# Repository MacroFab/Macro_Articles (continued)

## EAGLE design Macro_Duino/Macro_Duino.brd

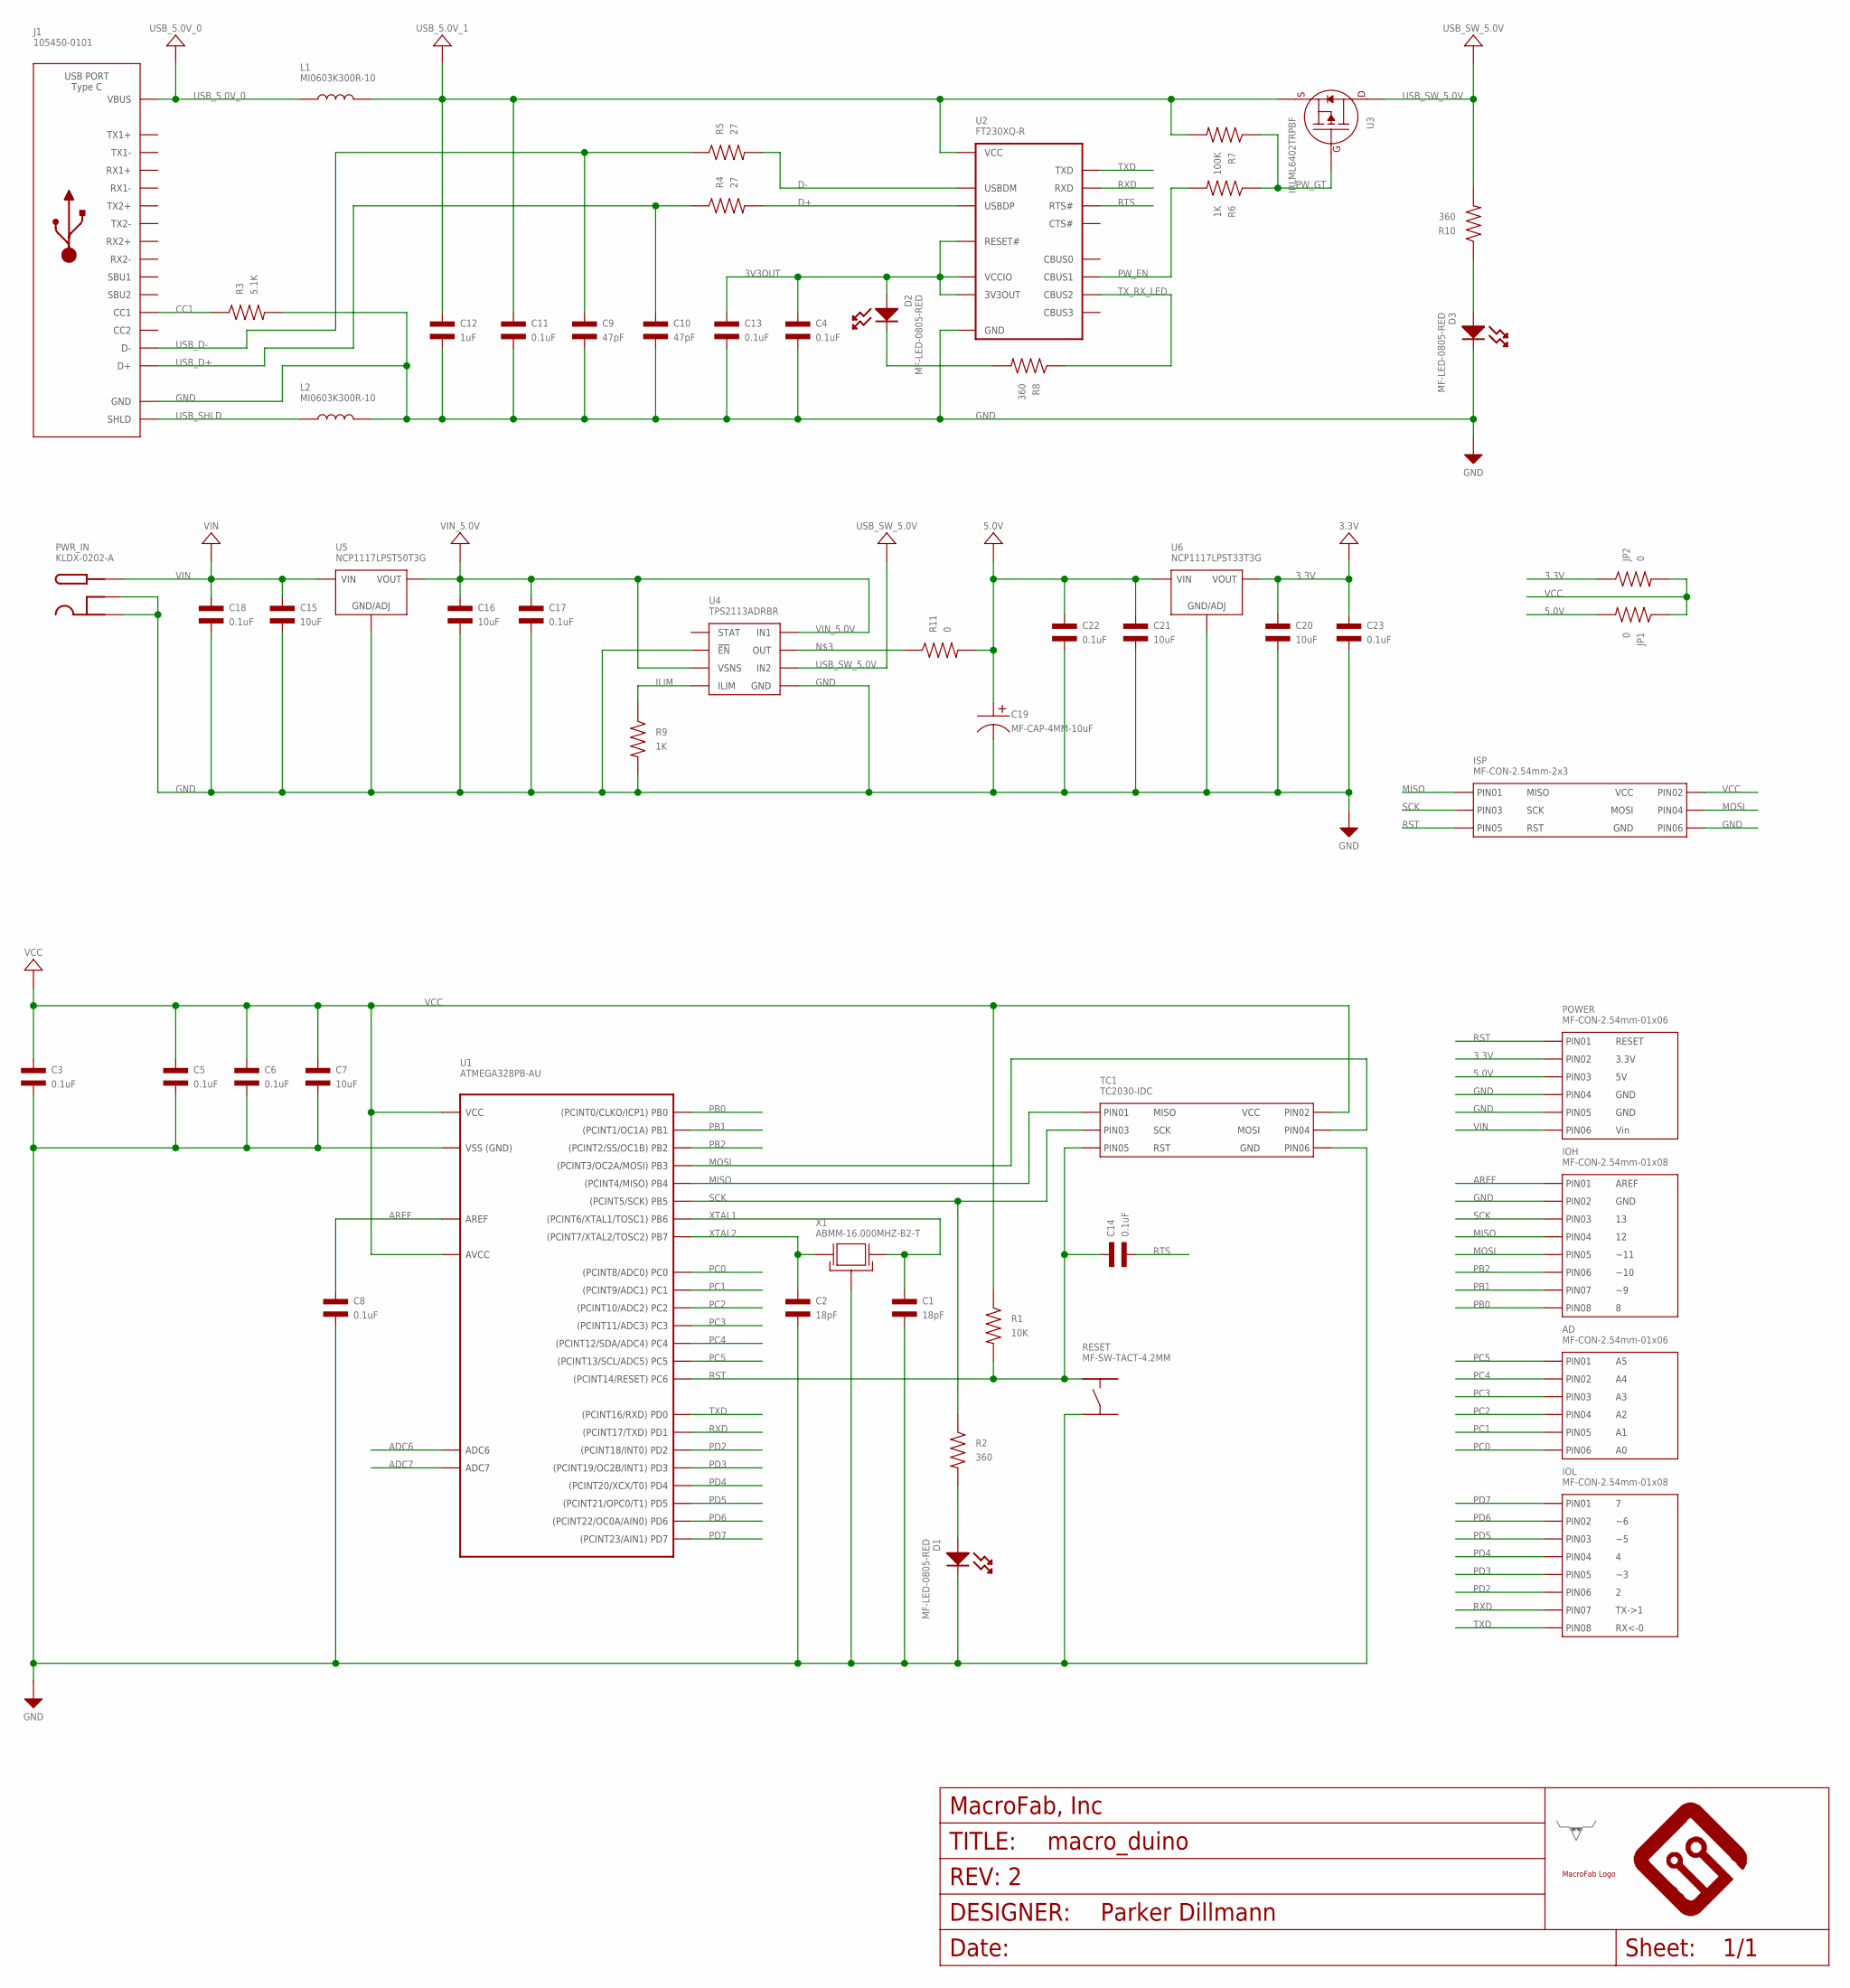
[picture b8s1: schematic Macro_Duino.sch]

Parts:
AD: MF-CON-2.54mm-01x06; PTH_2.54MM_01X06
C1, C2: 18pF; C0603; MPN VJ0603A180JXACW1BC
C3, C4, C5, C6, C8, C11, C13, C14, C17, C18, C22, C23: 0.1uF; C0603; MPN MF-CAP-0603-0.1uF
C7, C15, C16, C20, C21: 10uF; C1206; MPN MF-CAP-1206-10uF
C9, C10: 47pF; C0603; MPN 06035A470JAT2A
C12: 1uF; C0603; MPN MF-CAP-0603-1uF
C19: MF-CAP-4MM-10uF; CP4MM; MPN MF-CAP-4MM-10uF
D1, D2, D3: MF-LED-0805-RED; LED0805
FRAME1: MF_FRAMEDEFAULT; MF_FRAME_DEFAULT
IOH: MF-CON-2.54mm-01x08; PTH_2.54MM_01X08
IOL: MF-CON-2.54mm-01x08; PTH_2.54MM_01X08
ISP: MF-CON-2.54mm-2x3; PTH_2.54MM_02X03
J1: 105450-0101; MPN 105450-0101
JP1, JP2: 0; R0805; MPN MF-RES-0805-0
L1, L2: MI0603K300R-10; L0603; MPN MI0603K300R-10
POWER: MF-CON-2.54mm-01x06; PTH_2.54MM_01X06
PWR_IN: KLDX-0202-A; DC_PWR_JACK
R1: 10K; R0603; MPN MF-RES-0603-10K
R2, R8, R10: 360; R0603; MPN MF-RES-0603-360
R3: 5.1K; R0603; MPN CR0603-FX-5101ELF
R4, R5: 27; R0603; MPN MF-RES-0603-27
R6, R9: 1K; R0603; MPN MF-RES-0603-1K
R7: 100K; R0603; MPN MF-RES-0603-100K
R11: 0; R0805; MPN MF-RES-0805-0
RESET: MF-SW-TACT-4.2MM; TACT4.2MM
TC1: TC2030-IDC; TC2030-IDC-FP
U1: ATMEGA328PB-AU; TQFP32; MPN ATMEGA328PB-AU
U2: FT230XQ-R; FT230X_QFN-16; MPN FT230XQ-R
U3: IRLML6402TRPBF; SOT-23-3
U4: TPS2113ADRBR; TPS211X_SON-8; MPN TPS2113ADRBR
U5: NCP1117LPST50T3G; SOT-223-3
U6: NCP1117LPST33T3G; SOT-223-3
U$14: MF_LOGOLOGO; MF_LOGO
U$15: LHE_LOGOLHE_LOGO; LHE_LOGO
X1: ABMM-16.000MHZ-B2-T; 7MMX5MM; MPN ABMM-16.000MHZ-B2-T

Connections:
3.3V: C20.P$1, C23.P$1, JP2.P$1, POWER.P$2 (PIN2), U6.P$1 (VOUT), U6.P$3 (VOUT)
3V3OUT: C4.P$1, C13.P$1, D2.ANODE, U2.1 (VCCIO), U2.8 (3V3OUT), U2.9 (RESET#)
5.0V: C19.P$1, C21.P$1, C22.P$1, JP1.P$2, POWER.P$3 (PIN3), R11.P$2, U6.P$4 (VIN)
ADC6: U1.P$19 (ADC6)
ADC7: U1.P$22 (ADC7)
AREF: C8.P$1, IOH.P$1 (PIN1), U1.P$20 (AREF)
CC1: J1.A5 (CC1), R3.P$1
D+: R4.P$2, U2.6 (USBDP)
D-: R5.P$2, U2.7 (USBDM)
GND: C1.P$2, C2.P$2, C3.P$2, C4.P$2, C5.P$2, C6.P$2, C7.P$2, C8.P$2, C9.P$2, C10.P$2, C11.P$2, C12.P$2, C13.P$2, C15.P$2, C16.P$2, C17.P$2, C18.P$2, C19.P$2, C20.P$2, C21.P$2, C22.P$2, C23.P$2, D1.CATHODE, D3.CATHODE, IOH.P$2 (PIN2), ISP.P$6 (PIN6), J1.A1 (GND), J1.A12 (GND), J1.B1 (GND), J1.B12 (GND), L2.P$2, POWER.P$4 (PIN4), POWER.P$5 (PIN5), PWR_IN.SLEEVE1 (SLEEVE), PWR_IN.SLEEVE2 (SLEEVE_SHUNT), R3.P$2, R9.P$2, RESET.P$3, TC1.P$6 (PIN6), U1.P$3 (GND), U1.P$5 (GND), U1.P$21 (GND), U2.3 (GND), U2.13 (GND), U2.PAD (GND), U4.2 (!EN), U4.5 (GND), U4.PAD (GND), U5.P$2 (GND/ADJ), U6.P$2 (GND/ADJ), X1.P$2 (GND), X1.P$4 (GND)
ILIM: R9.P$1, U4.4 (ILIM)
MISO: IOH.P$4 (PIN4), ISP.P$1 (PIN1), TC1.P$1 (PIN1), U1.P$16 (PB4)
MOSI: IOH.P$5 (PIN5), ISP.P$4 (PIN4), TC1.P$4 (PIN4), U1.P$15 (PB3)
unnamed: D3.ANODE, R10.P$1
unnamed: D1.ANODE, R2.P$2
unnamed: R11.P$1, U4.7 (OUT)
unnamed: D2.CATHODE, R8.P$2
PB0: IOH.P$8 (PIN8), U1.P$12 (PB0)
PB1: IOH.P$7 (PIN7), U1.P$13 (PB1)
PB2: IOH.P$6 (PIN6), U1.P$14 (PB2)
PC0: AD.P$6 (PIN6), U1.P$23 (PC0)
PC1: AD.P$5 (PIN5), U1.P$24 (PC1)
PC2: AD.P$4 (PIN4), U1.P$25 (PC2)
PC3: AD.P$3 (PIN3), U1.P$26 (PC3)
PC4: AD.P$2 (PIN2), U1.P$27 (PC4)
PC5: AD.P$1 (PIN1), U1.P$28 (PC5)
PD2: IOL.P$6 (PIN6), U1.P$32 (PD2)
PD3: IOL.P$5 (PIN5), U1.P$1 (PD3)
PD4: IOL.P$4 (PIN4), U1.P$2 (PD4)
PD5: IOL.P$3 (PIN3), U1.P$9 (PD5)
PD6: IOL.P$2 (PIN2), U1.P$10 (PD6)
PD7: IOL.P$1 (PIN1), U1.P$11 (PD7)
PW_EN: R6.P$2, U2.11 (CBUS1)
PW_GT: R6.P$1, R7.P$1, U3.1 (GATE)
RST: C14.P$1, ISP.P$5 (PIN5), POWER.P$1 (PIN1), R1.P$2, RESET.P$1, TC1.P$5 (PIN5), U1.P$29 (PC6)
RTS: C14.P$2, U2.16 (RTS#)
RXD: IOL.P$7 (PIN7), U1.P$31 (PD1), U2.2 (RXD)
SCK: IOH.P$3 (PIN3), ISP.P$3 (PIN3), R2.P$1, TC1.P$3 (PIN3), U1.P$17 (PB5)
TXD: IOL.P$8 (PIN8), U1.P$30 (PD0), U2.15 (TXD)
TX_RX_LED: R8.P$1, U2.5 (CBUS2)
USB_5.0V_0: J1.A4 (VBUS), J1.A9 (VBUS), J1.B4 (VBUS), J1.B9 (VBUS), L1.P$1
USB_5.0V_1: C11.P$1, C12.P$1, L1.P$2, R7.P$2, U2.10 (VCC), U3.2 (SOURCE)
USB_D+: C10.P$1, J1.A6 (D+), J1.B6 (D+), R4.P$1
USB_D-: C9.P$1, J1.A7 (D-), J1.B7 (D-), R5.P$1
USB_SHLD: J1.S_T1 (SHLD), J1.S_T2 (SHLD), J1.S_T3 (SHLD), J1.S_T4 (SHLD), L2.P$1
USB_SW_5.0V: R10.P$2, U3.3 (DRAIN), U4.6 (IN2)
VCC: C3.P$1, C5.P$1, C6.P$1, C7.P$1, ISP.P$2 (PIN2), JP1.P$1, JP2.P$2, R1.P$1, TC1.P$2 (PIN2), U1.P$4 (VCC), U1.P$6 (VCC), U1.P$18 (AVCC)
VIN: C15.P$1, C18.P$1, POWER.P$6 (PIN6), PWR_IN.PIN, U5.P$4 (VIN)
VIN_5.0V: C16.P$1, C17.P$1, U4.3 (VSNS), U4.8 (IN1), U5.P$1 (VOUT), U5.P$3 (VOUT)
XTAL1: C1.P$1, U1.P$7 (PB6), X1.P$3 (X1)
XTAL2: C2.P$1, U1.P$8 (PB7), X1.P$1 (X0)

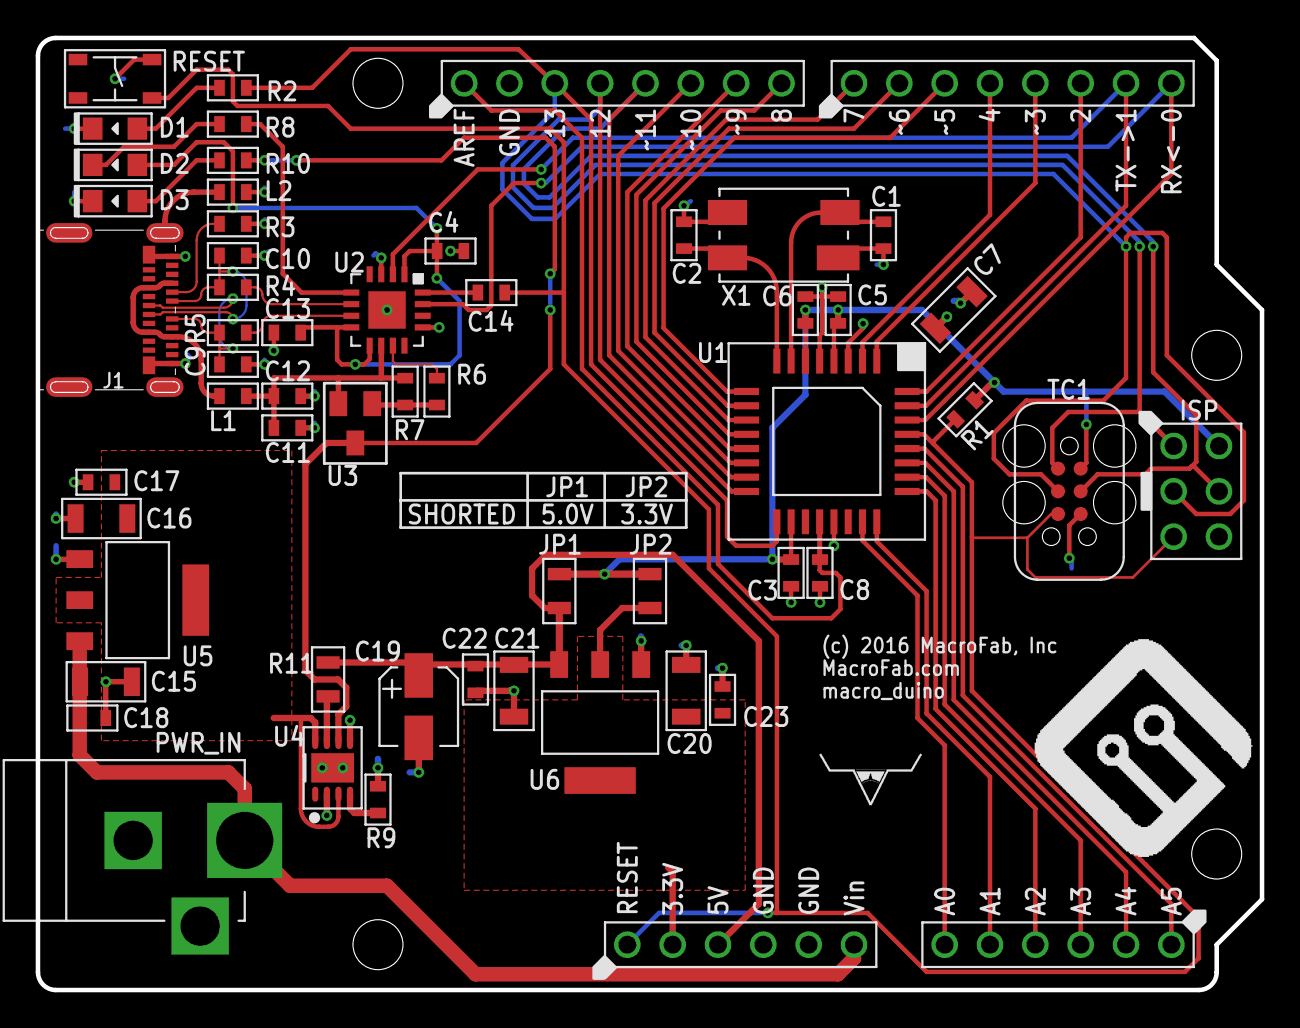
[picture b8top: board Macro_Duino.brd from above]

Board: 2 copper layers, 68.6 x 53.3 mm, 60 parts (0 on the bottom side), 49 nets.

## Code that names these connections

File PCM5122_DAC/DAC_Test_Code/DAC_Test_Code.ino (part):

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
//enable and path control the TS3A5018PWR analog switchs. 
const int enable = 6; //active low
const int path = 5;
//pwr_on is connected to the power switcher that turns the power to the PCM5122 DAC board on and off. 
const int pwr_on = 4; //active high
//Button on the fixture
const int btn = 7;

//Samples from the DAC via analog read are stored here
int16_t record_R[DATA_SIZE];
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{
  Wire.begin();

  pinMode(pwr_on,OUTPUT);
  pinMode(path,OUTPUT);
  pinMode(enable,OUTPUT);

  Serial.begin(2000000);
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
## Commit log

2016-05-02 SPF article Files
2016-05-02 Update sketchup file.
2016-08-10 moving all the boards here
2016-08-10 Major revamp of repo.
2016-08-10 Adding board images.
2016-08-11 Adding example code to AVR_Tag-Connect
2016-08-11 Working on EFM8 Tag Connect Example. Not compelte.
2016-08-12 Finished EFM8 board.
2016-08-12 Finished board.
2016-08-17 Fixing the Type C connector.
2016-08-17 Finishing up the board design.
2016-08-22 Updated to recent library changes.
2016-08-23 Working on Macro_Duino
2016-08-30 Almost done with Macro Duino
2016-08-30 Complete!~
2016-09-02 Fixed MISO/MOSI swap on 10Pin ISP header.
2016-09-13 Added Pin sharing support for TagConnect.
2016-09-20 removed backup file that snuck in
2016-09-30 Fixed FTDI power issue.
2016-09-30 Added SWD2TC
2016-10-03 Updating Readme and added files for SWD2TC
2017-08-18 Adding Blink code!
2017-09-08 Adding Resistor Resistor!
2018-04-30 Added PCM5122 For DAC articles
2018-05-21 Added DAC test code for the fixture
2018-05-31 adding code for the ethanol sensor
2018-07-13 MFG files for MEP SAO DC 26 Complete
    Will do readme.md for this later
2018-07-13 Zip file for MFG files
2018-07-30 Adding Software for MEP SAO
2019-01-18 Adding new USB Type-C templates
2019-01-29 Finished the FTDI_FT230X Example
    Prop has been added and a header to monitor the current off the USB buss
2019-01-29 cleaned up schematic
2019-01-30 images for the layout
2019-01-30 Added MPNs and normalized part values
2019-01-30 Forgot a MPN :)
2019-02-04 no complete
2019-02-05 USB connections made.
2019-02-07 Schematic complete. Parts placed.
2019-02-08 Routing complete
2019-02-08 PCB complete. First rev ordered.
2019-02-21 Fixed IP4234CZ6 ESD protection
2019-02-22 Update ATmega32u4_Example.brd
    Cleaned up silkscreen
2019-05-31 REV 2. Fixed USB ESD protection.
2019-07-17 updated with two (2 :O ) CC resistors
